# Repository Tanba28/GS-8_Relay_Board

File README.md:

# GS-8_Relay_Board
GS-8 Relay Board

Master project -> [project-arrows/GS-8](https://github.com/project-arrows/GS-8)
## Overview
 * 電源・CANバスの中継ボード

## Role
 * PowerManagement Boardからの電源を各モジュール基板に中継する。
 * CANバスを中継する。

## Link
 * [Tanba28/GS-8_PM_Board](https://github.com/Tanba28/GS-8_PM_Board)
 * [Tanba28/GS-8_PD_Board](https://github.com/Tanba28/GS-8_PD_Board)
 * [Tanba28/GS-8_Barometer](https://github.com/Tanba28/GS-8_Barometer)
 * [Tanba28/GS-8_Motion_Logger](https://github.com/Tanba28/GS-8_Motion_Logger)
 * [ringo156/GS-8_ACCLRM_Board](https://github.com/ringo156/GS-8_ACCLRM_Board)
 * [takamasavvv/RCT-X_Logger](https://github.com/takamasavvv/RCT-X-Logger)
 * [takamasavvv/RCT-X-Telemetry](https://github.com/takamasavvv/RCT-X-Telemetry)
 
## LICENSE
MIT License

Copyright (c) 2019 Tanba28

Permission is hereby granted, free of charge, to any person obtaining a copy
of this software and associated documentation files (the "Software"), to deal
in the Software without restriction, including without limitation the rights
to use, copy, modify, merge, publish, distribute, sublicense, and/or sell
copies of the Software, and to permit persons to whom the Software is
furnished to do so, subject to the following conditions:

The above copyright notice and this permission notice shall be included in all
copies or substantial portions of the Software.

THE SOFTWARE IS PROVIDED "AS IS", WITHOUT WARRANTY OF ANY KIND, EXPRESS OR
IMPLIED, INCLUDING BUT NOT LIMITED TO THE WARRANTIES OF MERCHANTABILITY,
FITNESS FOR A PARTICULAR PURPOSE AND NONINFRINGEMENT. IN NO EVENT SHALL THE
AUTHORS OR COPYRIGHT HOLDERS BE LIABLE FOR ANY CLAIM, DAMAGES OR OTHER
LIABILITY, WHETHER IN AN ACTION OF CONTRACT, TORT OR OTHERWISE, ARISING FROM,
OUT OF OR IN CONNECTION WITH THE SOFTWARE OR THE USE OR OTHER DEALINGS IN THE
SOFTWARE.

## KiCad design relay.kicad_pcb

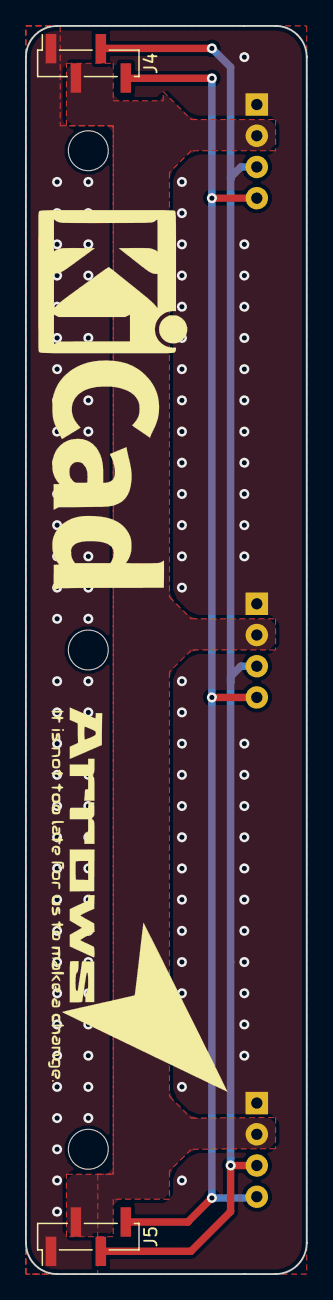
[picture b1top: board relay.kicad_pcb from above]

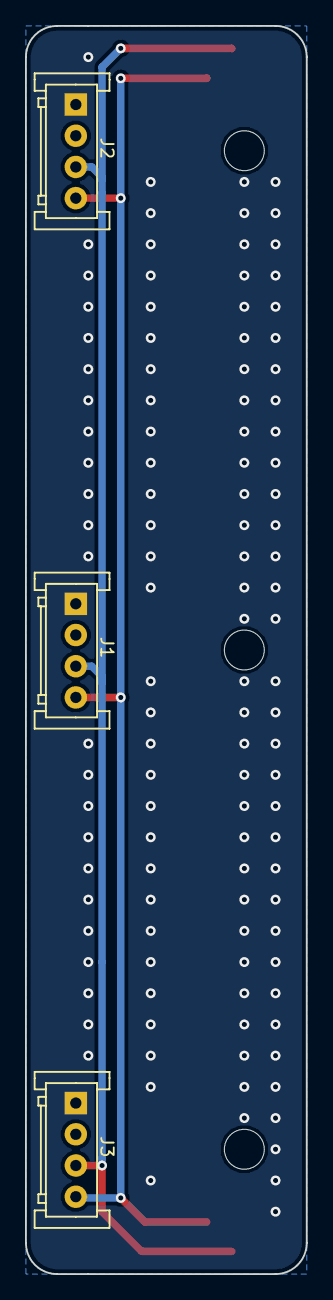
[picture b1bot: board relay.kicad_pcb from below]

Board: 2 copper layers, 22.5 x 100.0 mm, 5 parts (3 on the bottom side), 4 nets.

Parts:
J1, J2, J3: Port; JST_JQ_04JQ-BT_1x04_P2.5mm_Vertical
J4: Connet; PinHeader_1x04_P2.00mm_Vertical_SMD_Pin1Right
J5: Connet; PinHeader_1x04_P2.00mm_Vertical_SMD_Pin1Left

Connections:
/CANH: J1.3, J2.3, J3.3, J4.3, J5.3
/CANL: J1.4, J2.4, J3.4, J4.4, J5.4
GND: J1.1, J2.1, J3.1, J4.1, J5.1
VCC: J1.2, J2.2, J3.2, J4.2, J5.2

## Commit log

2019-10-12 [add] ハード完成。ガーバー出力
2019-10-12 [add] 画像を追加
